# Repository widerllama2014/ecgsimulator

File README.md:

# Simulador de señales biomédicas (ECG)

Simulador educativo de señales de electrocardiograma (ECG) basado en **ESP32-S3**.
Funciona como **fuente de prueba segura** para equipos de adquisición (lector del
Proyecto 4) y como material de estudio. **No se conecta a personas.**

> Proyecto 5 — *Simulador de señales biomédicas* del banco de proyectos del curso.

## Equipo

| Integrante | Correo | Rol principal |
|---|---|---|
| Benjamín Garrido | b.garridob@udd.cl | Construcción física, esquemático/PCB/BOM, pruebas |
| José Tomás Romero | jt.romeroreyes@udd.cl | Electrónica/investigación, firmware/software, documentación y repositorio |

- **Curso:** Electrónica Biomédica — IBB224S-1, Universidad del Desarrollo (UDD)
- **Docentes:** Alejandro Rebolledo, Wladimir

## Descripción y arquitectura

El sistema se organiza en **tres partes**:

1. **Prototipo físico (esta PCB).** ESP32-S3-DevKitC-1 (montado por headers) + batería.
   Genera la señal por **PWM → filtro RC** y la lleva a nivel fisiológico mediante un
   **divisor/atenuador** y una **red de resistencias** que la reparte en los bornes de
   electrodos **RA / LA / LL / RL(N)**, obteniendo las 3 derivaciones bipolares
   **DI, DII, DIII**. Incluye LEDs de estado (encendido, Bluetooth, batería), punto de
   prueba en volts y 3 conectores: **USB**, **cargador de batería** y **salida a
   osciloscopio (BNC)**. *Los conectores anteriores no son las salidas de ECG.*
2. **Software (teléfono/PC).** Procesamiento, visualización, interfaz y selección/
   modificación de la señal simulada y de las interferencias.
3. **Comunicación.** Enlace ESP32-S3 ↔ equipo externo mediante **Bluetooth (BLE)**.

```
[Software PC/Teléfono] <--BLE--> [ESP32-S3] --PWM--> [Filtro RC] --> TP1 (volts, BNC)
                                                          |
                                                 [Divisor/atenuador]
                                                          |
                                             [Red de resistencias] --> RA / LA / LL / RL(N)
```

## Estructura del repositorio

```
.
├── README.md
├── LICENSE
├── docs/
│   ├── datasheets/      Hojas de datos de los componentes
│   ├── bitacora.md      Registro de avances
│   └── informes/        Informes de entrega (Parte I, II, ...)
├── electronica/
│   ├── kicad/           Proyecto editable de KiCad (.kicad_pro/.sch/.pcb)
│   ├── libraries/       Símbolos, footprints y modelos 3D propios o verificados
│   └── outputs/         Exportables: PDF, Gerbers, drill, BOM, STEP, vistas 3D
├── firmware/            Código del ESP32-S3
└── software/            Aplicación de PC/teléfono
```

## Estado del proyecto

- **Parte I (propuesta y requerimientos):** entregada — ver `docs/informes/`.
- **Parte II (diseño electrónico y PCB):** en desarrollo.
  - [x] Red pasiva (filtro RC + divisor + bornes) iniciada en el esquemático.
  - [ ] Integración del ESP32-S3, alimentación (batería + carga), LEDs y conectores.
  - [ ] Bibliotecas propias verificadas.
  - [ ] Layout según reglas CNC del laboratorio.
  - [ ] Exportables y DRC limpio.

## Reglas de fabricación (CNC del laboratorio)

El diseño debe respetar, de forma obligatoria:

- Ancho mínimo de pista: **0,8 mm**.
- Separación mínima (cobre–cobre): **0,8 mm**.
- Cuatro agujeros de montaje de **3,2 mm** cerca de las esquinas.
- Ruteo priorizado en una sola cara (**B.Cu**); componentes **THT**.

## Licencia

Este proyecto es **hardware abierto** bajo la **CERN Open Hardware Licence
Version 2 – Strongly Reciprocal (CERN-OHL-S v2)** — ver [LICENSE](LICENSE).

Qué permite y qué exige:

- ✅ **Usar, estudiar, modificar, fabricar, distribuir y vender** el diseño y los
  productos basados en él. La **publicidad** está permitida.
- 🔁 **Recíproca fuerte (copyleft):** toda variación o derivado debe licenciarse
  también bajo CERN-OHL-S v2 — es decir, **toda variación sigue siendo hardware
  abierto**.
- 📝 Debes **conservar los avisos (Notices)** de copyright y autoría, e indicar tus
  modificaciones (fecha y descripción breve).
- 🔗 Debes **dar acceso al diseño fuente** (Source Location) del original y de tus
  variaciones; si fabricas un producto, debes entregar la fuente o notificar dónde
  obtenerla, y — si así se indica — mostrar la ubicación fuente en el producto o su
  empaque (sección 4).

**Aviso para incluir en el diseño / producto (Source Location = redirección al proyecto):**

```
Copyright 2026 Benjamín Garrido, José Tomás Romero

This source describes Open Hardware and is licensed under the CERN-OHL-S v2.
You may redistribute and modify this source and make products using it under
the terms of the CERN-OHL-S v2 (https://ohwr.org/cern_ohl_s_v2.txt).
This source is distributed WITHOUT ANY EXPRESS OR IMPLIED WARRANTY, INCLUDING OF
MERCHANTABILITY, SATISFACTORY QUALITY AND FITNESS FOR A PARTICULAR PURPOSE.
Please see the CERN-OHL-S v2 for applicable conditions.
Source Location: https://github.com/widerllama2014/ecgsimulator
```

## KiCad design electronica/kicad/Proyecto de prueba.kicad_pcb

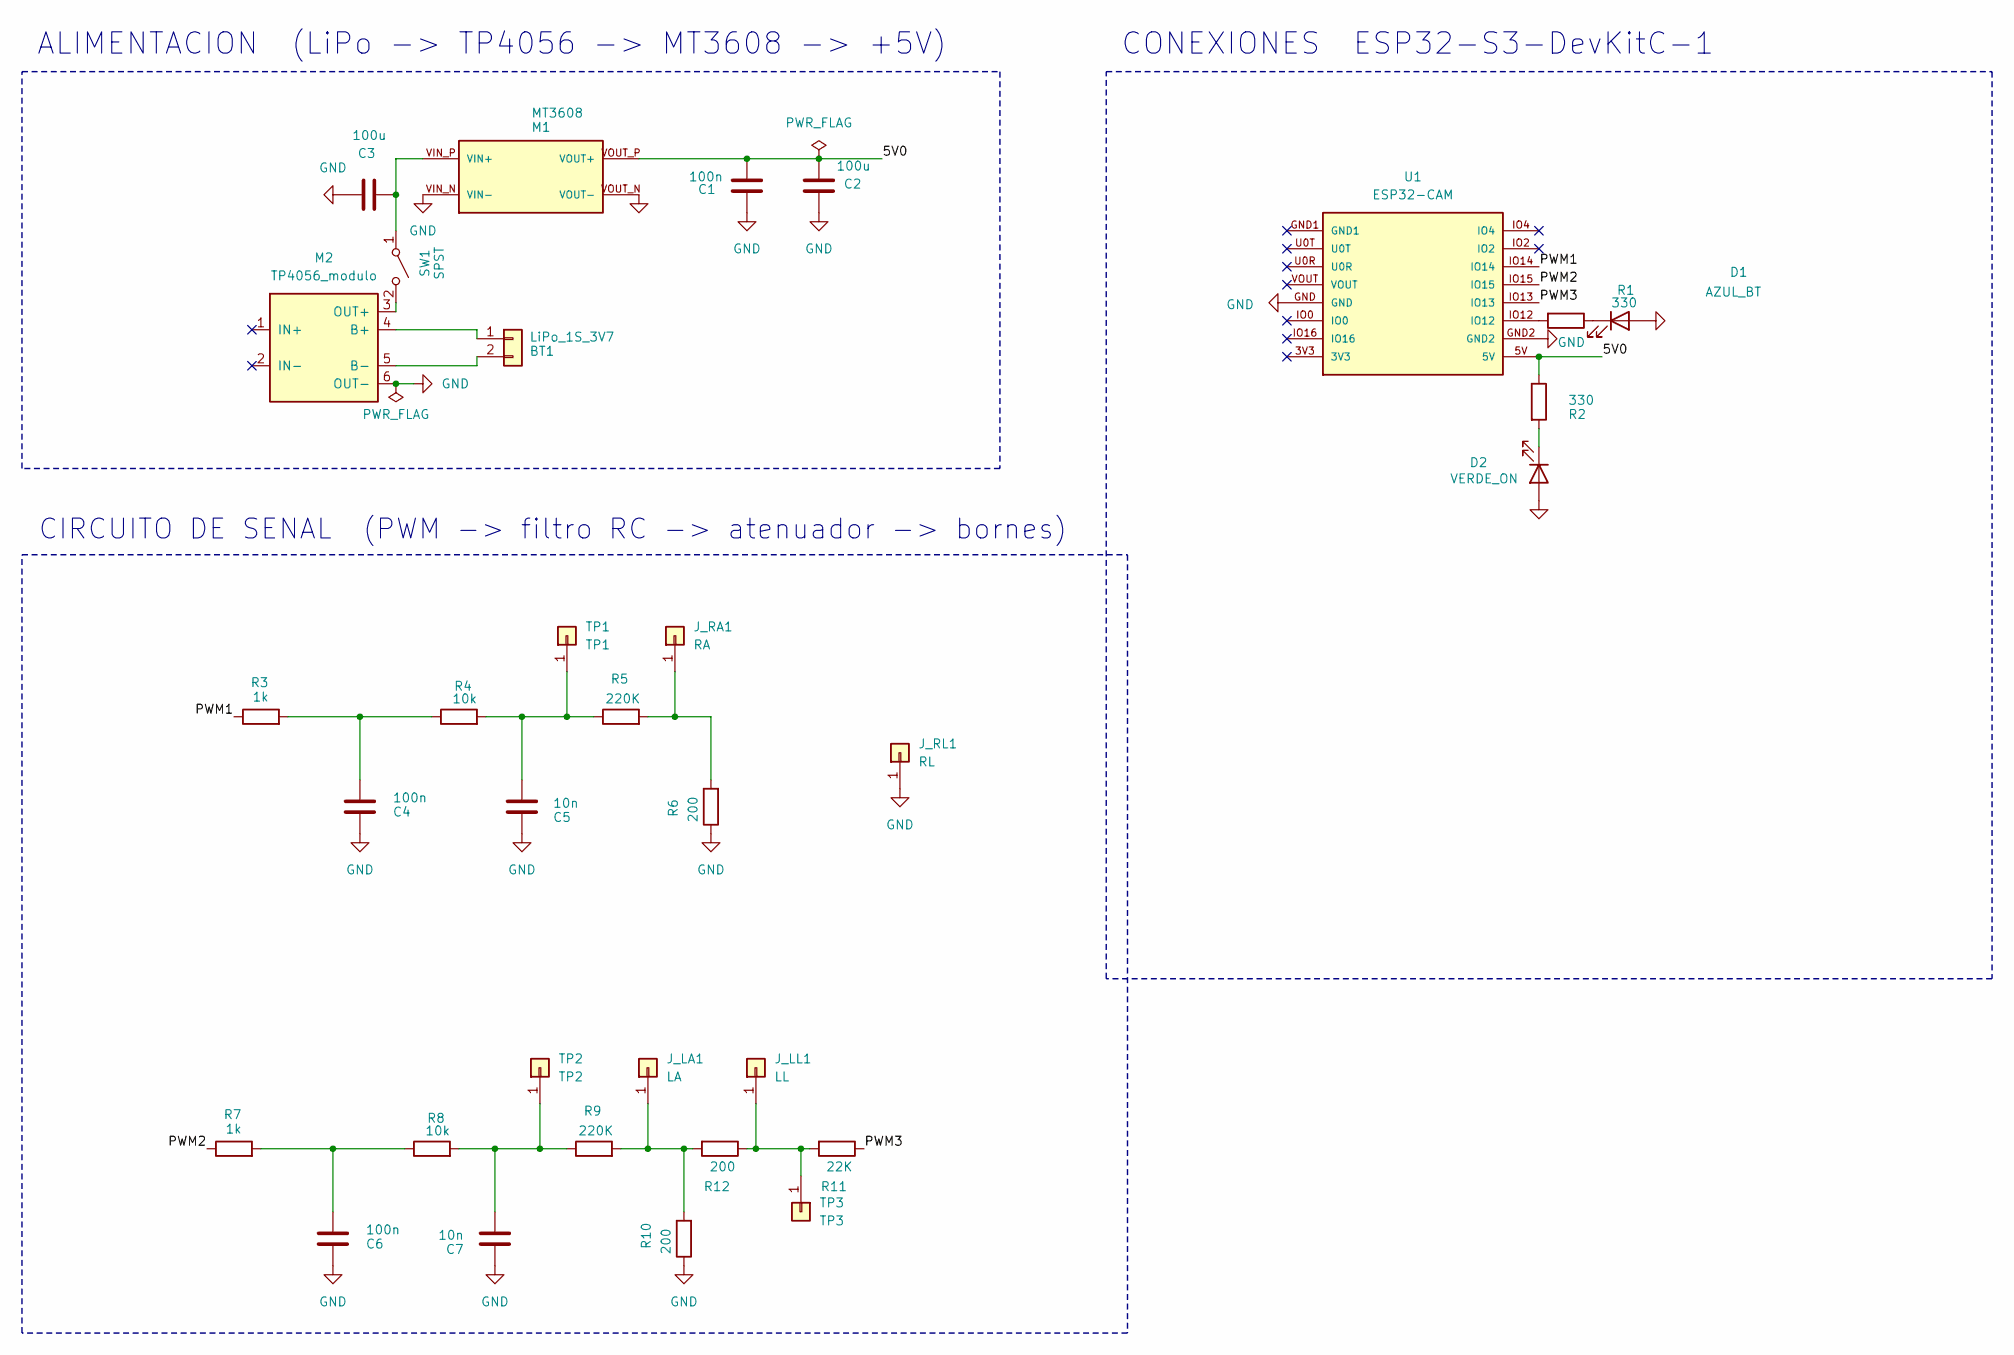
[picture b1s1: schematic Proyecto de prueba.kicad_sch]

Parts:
BT1: LiPo_1S_3V7; JST_PH_B2B-PH-K_1x02_P2.00mm_Vertical
C1, C4, C6: 100n; C_Disc_D5.0mm_W2.5mm_P2.50mm
C2, C3: 100u; CP_Radial_D6.3mm_P2.50mm
C5, C7: 10n; C_Disc_D5.0mm_W2.5mm_P2.50mm
D1: AZUL_BT; LED_D5.0mm
D2: VERDE_ON; LED_D5.0mm
J_LA1: LA; TestPoint_THTPad_D2.0mm_Drill1.0mm
J_LL1: LL; TestPoint_THTPad_D2.0mm_Drill1.0mm
J_RA1: RA; TestPoint_THTPad_D2.0mm_Drill1.0mm
J_RL1: RL; TestPoint_THTPad_D2.0mm_Drill1.0mm
M1: MT3608; MT3608_DC
M2: TP4056_modulo
R1, R2: 330; R_Axial_DIN0207_L6.3mm_D2.5mm_P10.16mm_Horizontal
R3, R7: 1k; R_Axial_DIN0207_L6.3mm_D2.5mm_P10.16mm_Horizontal
R4, R8: 10k; R_Axial_DIN0207_L6.3mm_D2.5mm_P10.16mm_Horizontal
R5, R9: 220K; R_Axial_DIN0207_L6.3mm_D2.5mm_P10.16mm_Horizontal
R6, R10, R12: 200; R_Axial_DIN0207_L6.3mm_D2.5mm_P10.16mm_Horizontal
R11: 22K; R_Axial_DIN0207_L6.3mm_D2.5mm_P10.16mm_Horizontal
SW1: SPST; SW_Push_2P
TP1: TP1; TestPoint_THTPad_D2.0mm_Drill1.0mm
TP2: TP2; TestPoint_THTPad_D2.0mm_Drill1.0mm
TP3: TP3; TestPoint_THTPad_D2.0mm_Drill1.0mm
U1: ESP32-CAM

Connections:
/5V0: C1.2, C2.1, M1.VOUT_P (VOUT+), R2.1, U1.5V
/PWM1: R3.1, U1.IO14
/PWM2: R7.1, U1.IO15
/PWM3: R11.1, U1.IO13
GND: C1.1, C2.2, C3.2, C4.2, C5.2, C6.2, C7.2, D1.2 (A), D2.2 (A), J_RL1.1 (Pin_1_1), M1.VIN_N (VIN-), M1.VOUT_N (VOUT-), M2.6 (OUT-), R6.1, R10.1, U1.GND, U1.GND2
unnamed: BT1.1, M2.4 (B+)
unnamed: BT1.2, M2.5 (B-)
unnamed: C4.1, R3.2, R4.1
unnamed: C6.1, R7.2, R8.1
unnamed: D1.1 (K), R1.1
unnamed: D2.1 (K), R2.2
unnamed: J_LA1.1 (Pin_1_1), R9.2, R10.2, R12.2
unnamed: J_LL1.1 (Pin_1_1), R11.2, R12.1, TP3.1 (Pin_1_1)
unnamed: J_RA1.1 (Pin_1_1), R5.2, R6.2
unnamed: C3.1, M1.VIN_P (VIN+), SW1.1 (A)
unnamed: M2.3 (OUT+), SW1.2 (B)
unnamed: R1.2, U1.IO12
unnamed: C5.1, R4.2, R5.1, TP1.1 (Pin_1_1)
unnamed: C7.1, R8.2, R9.1, TP2.1 (Pin_1_1)

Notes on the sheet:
CIRCUITO DE SENAL (PWM -> filtro RC -> atenuador -> bornes)
CONEXIONES ESP32-S3-DevKitC-1
ALIMENTACION (LiPo -> TP4056 -> MT3608 -> +5V)

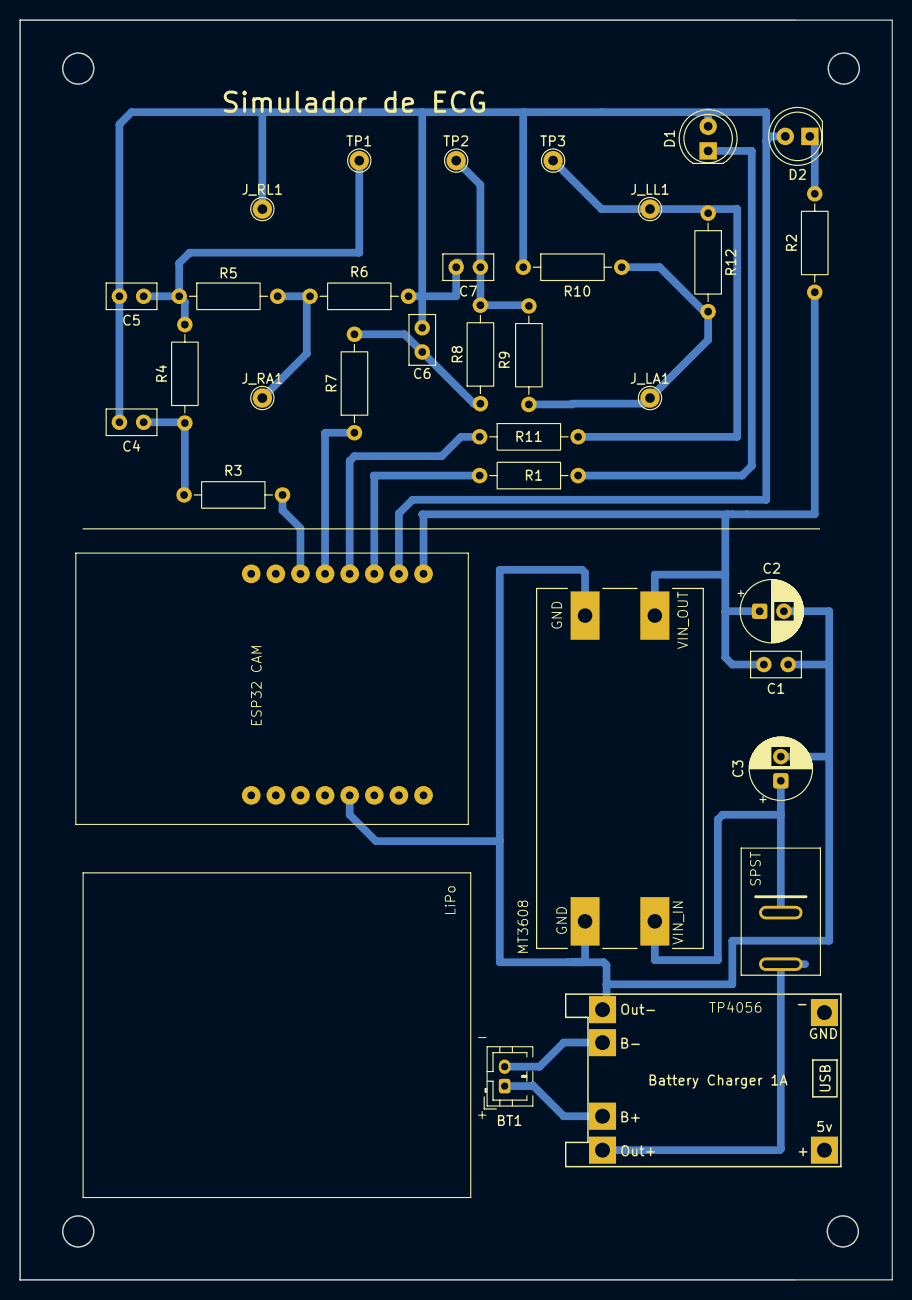
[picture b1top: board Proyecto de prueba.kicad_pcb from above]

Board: 2 copper layers, 90.0 x 130.0 mm, 33 parts (0 on the bottom side), 19 nets.
